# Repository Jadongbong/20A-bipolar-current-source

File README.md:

# Schine Group Bias Coils Current Controller
This repo provides information regarding the Bias Coils Current Controller (here on out referred to as “the controller”) used by the Schine Group at the Joint Quantum Institute (JQI) at University of Maryland, College Park. This is an experimental apparatus designed to drive Helmholtz coil pairs to cancel external magnetic fields which would otherwise disturb the experiment. The controller provides an output current proportional to an input voltage and features an ultra-low noise feedback circuit design for precise control of the output current down to the fractional mA level. The controller has three channels to independently control the magnetic fields along the x, y, and z axes.

## 20A-bipolar-current-source
This project is based on the [`20A-bipolar-current-source`](https://github.com/restelli/20A-bipolar-current-source) design of Mingshu Zhao and Alessandro Restelli. Details on the circuit can be found in their [research article in AIP Advances](https://doi.org/10.1063/5.0138145).

## Circuit files
There are several KiCad project folders within the `kicad` directory in this repo.
* `controller_board` contains the circuit board for the main controller board on which the analog PI feedback is located.
* `Controller_supply` contains the controller's on-board power supply circuit board (used for powering the controller boards)
* `H-bridge` is for the development of the MOT coil current controller (empty project as of Jun 06, 2024).
* `rear` contains the original, liquid-cooled cuircuit board design housing the power MOSFETs that control the coil current. (Not used in this controller)
* `SchineLab_CoilFET_Board` contains the modified, air-cooled circuit board design housing the power MOSFETs for coil current control. (Used in this controller)

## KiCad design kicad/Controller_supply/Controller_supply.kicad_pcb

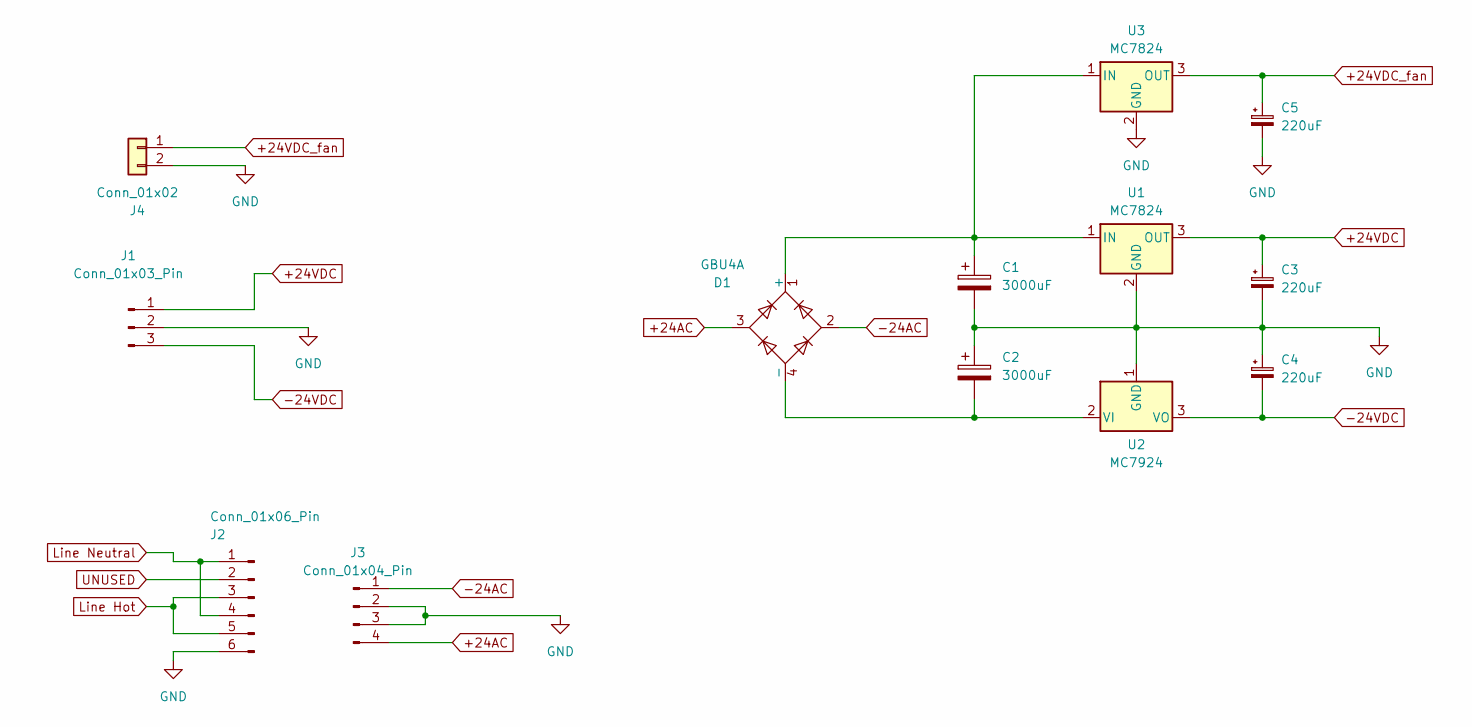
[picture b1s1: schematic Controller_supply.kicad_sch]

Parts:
C1, C2: 3000uF; CP_Elec_18x22; MPN EEE-FK1V302SV; DIGIKEY PARTNO P122523CT-ND
C3, C4, C5: 220uF; CP_Elec_10x10.5; MPN EEE-FK1H221P; DIGIKEY PARTNO PCE3812CT-ND
D1: GBU4A; Diode_Bridge_Vishay_GBU; MPN GBU4A; DIGIKEY PARTNO GBU4A-ND
J1: Conn_01x03_Pin; Generic_10.5x7.5mm-footprt_1x03_P3.50mm_Horizontal
J2: Conn_01x06_Pin
J3: Conn_01x04_Pin; Generic_pin-to-housing_1x04_P5.00mm_Horizontal
J4: Conn_01x02; Generic_7x7.5mm-footprt_1x02_P3.50mm_Horizontal
U1, U3: MC7824; TO-263-2; MPN MC7824CD2TR4G; DIGIKEY PARTNO MC7824CD2TR4GOSCT-ND
U2: MC7924; TO-263-2; MPN MC7924CD2TG; DIGIKEY PARTNO MC7924CD2TG-ND

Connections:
+24AC: D1.3, J3.4
+24VDC: C3.1, J1.1, U1.3 (OUT)
+24VDC_fan: C5.1, J4.1, U3.3 (OUT)
-24AC: D1.2, J3.1
-24VDC: C4.2, J1.3, U2.3 (VO)
GND: C1.2, C2.1, C3.2, C4.1, C5.2, J1.2, J2.6, J3.2, J3.3, J4.2, U1.2 (GND), U2.1 (GND), U3.2 (GND)
unnamed: C1.1, D1.1 (+), U1.1 (IN), U3.1 (IN)
unnamed: J2.1, J2.4
unnamed: J2.3, J2.5
unnamed: C2.2, D1.4 (-), U2.2 (VI)

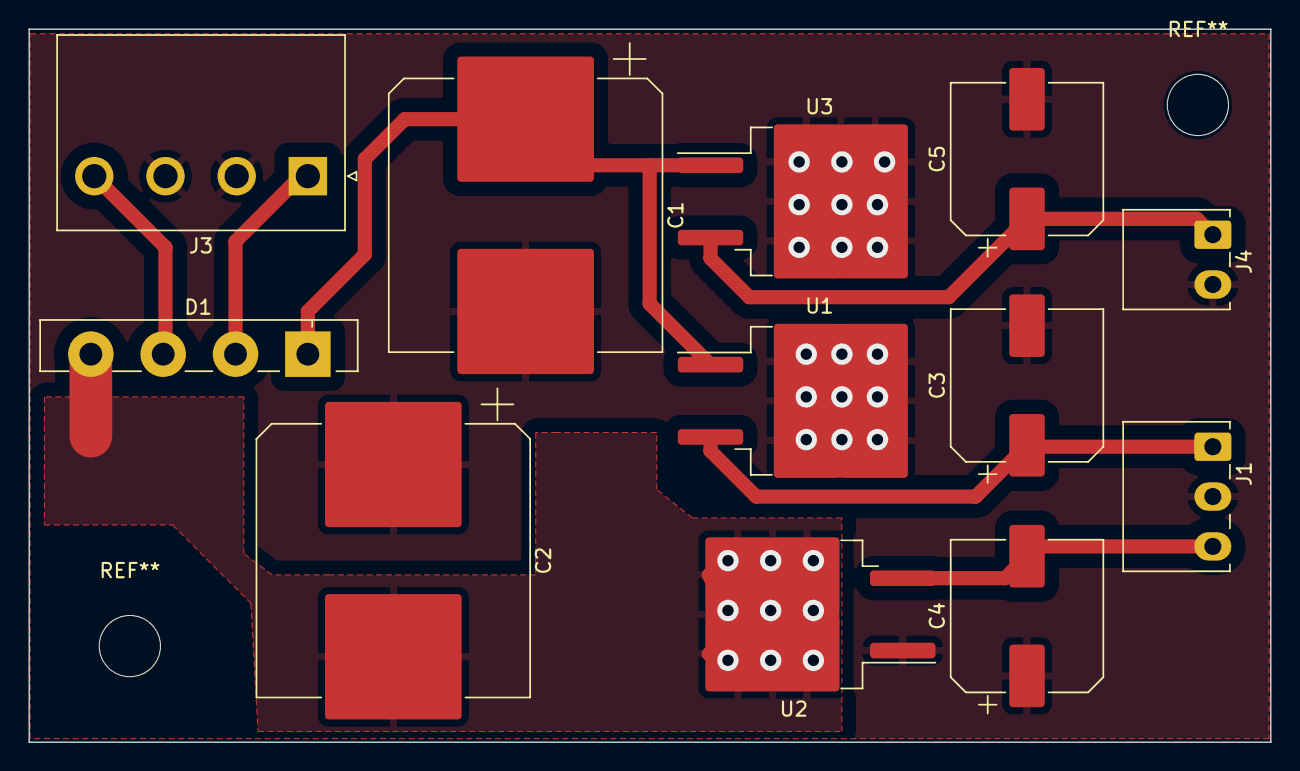
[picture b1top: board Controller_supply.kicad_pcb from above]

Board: 2 copper layers, 87.2 x 50.1 mm, 12 parts (0 on the bottom side), 8 nets.

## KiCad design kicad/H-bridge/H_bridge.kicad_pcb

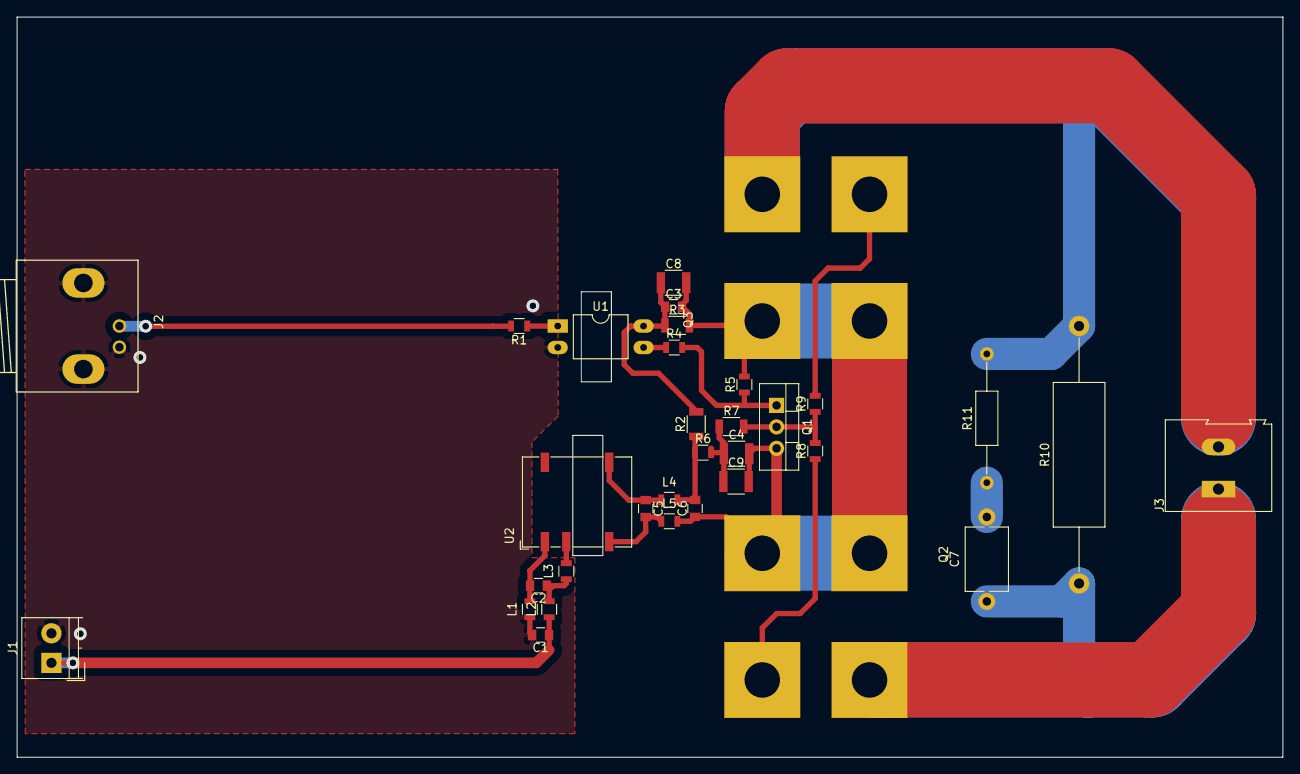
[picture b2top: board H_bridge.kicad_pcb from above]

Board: 2 copper layers, 149.9 x 87.6 mm, 33 parts (0 on the bottom side), 21 nets.

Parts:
C1, C2, C3, C5, C6: C; C_0805
C4, C8, C9: C; C_1210
C7: C; C_Disc_D7.5mm_W5.0mm_P10.00mm
J1: Screw_Terminal_01x02; TerminalBlock_4UCON_19963_02x3.5mm_Straight
J2: Conn_Coaxial; BNC_Socket_TYCO-AMP
J3: Screw_Terminal_01x02; TerminalBlock_Altech_AK300-2_P5.00mm
L1, L2, L3, L4, L5: INDUCTOR; L_0805
Q1: Q_NPN_Darlington_BCE; TO-220-3_Vertical
Q2, Q3: Q_NMOS_GDS; STE250NS10
R1, R4, R5, R6, R8, R9: R_US; R_0805
R2, R3, R7: R_US; R_1206
R10: R_US; R_Axial_DIN0617_L17.0mm_D6.0mm_P30.48mm_Horizontal
R11: R_US; R_Axial_DIN0207_L6.3mm_D2.5mm_P15.24mm_Horizontal
U1: LTV-817; DIP-4_W10.16mm_LongPads
U2: PDS1-S15-S15-M; DCDC-Conv_muRata_NXE2SxxxxMC

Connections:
+15V: C6.2, L4.2, R2.1, R6.1
GND: C1.2, J1.2, J2.2, L1.1, U1.2
GNDD: C3.2, C4.2, C6.1, C8.2, C9.2, L5.2, Q1.3, Q2.3, Q3.3, R3.2, R5.2
unnamed: C1.1, J1.1, L2.1
unnamed: C2.1, L2.2, L3.1
unnamed: C2.2, L1.2, U2.1
unnamed: C3.1, C8.1, R2.2, R3.1, U1.4
unnamed: C4.1, C9.1, R6.2, R7.1
unnamed: C5.1, L4.1, U2.8
unnamed: C5.2, L5.1, U2.7
unnamed: C7.1, J3.1, Q2.2, R10.1
unnamed: C7.2, R11.1
unnamed: J2.1, R1.2
unnamed: J3.2, Q3.2, R10.2, R11.2
unnamed: L3.2, U2.3
unnamed: Q1.1, R4.2, R5.1
unnamed: Q1.2, R7.2, R8.2, R9.1
unnamed: Q2.1, R8.1
unnamed: Q3.1, R9.2
unnamed: R1.1, U1.1
unnamed: R4.1, U1.3

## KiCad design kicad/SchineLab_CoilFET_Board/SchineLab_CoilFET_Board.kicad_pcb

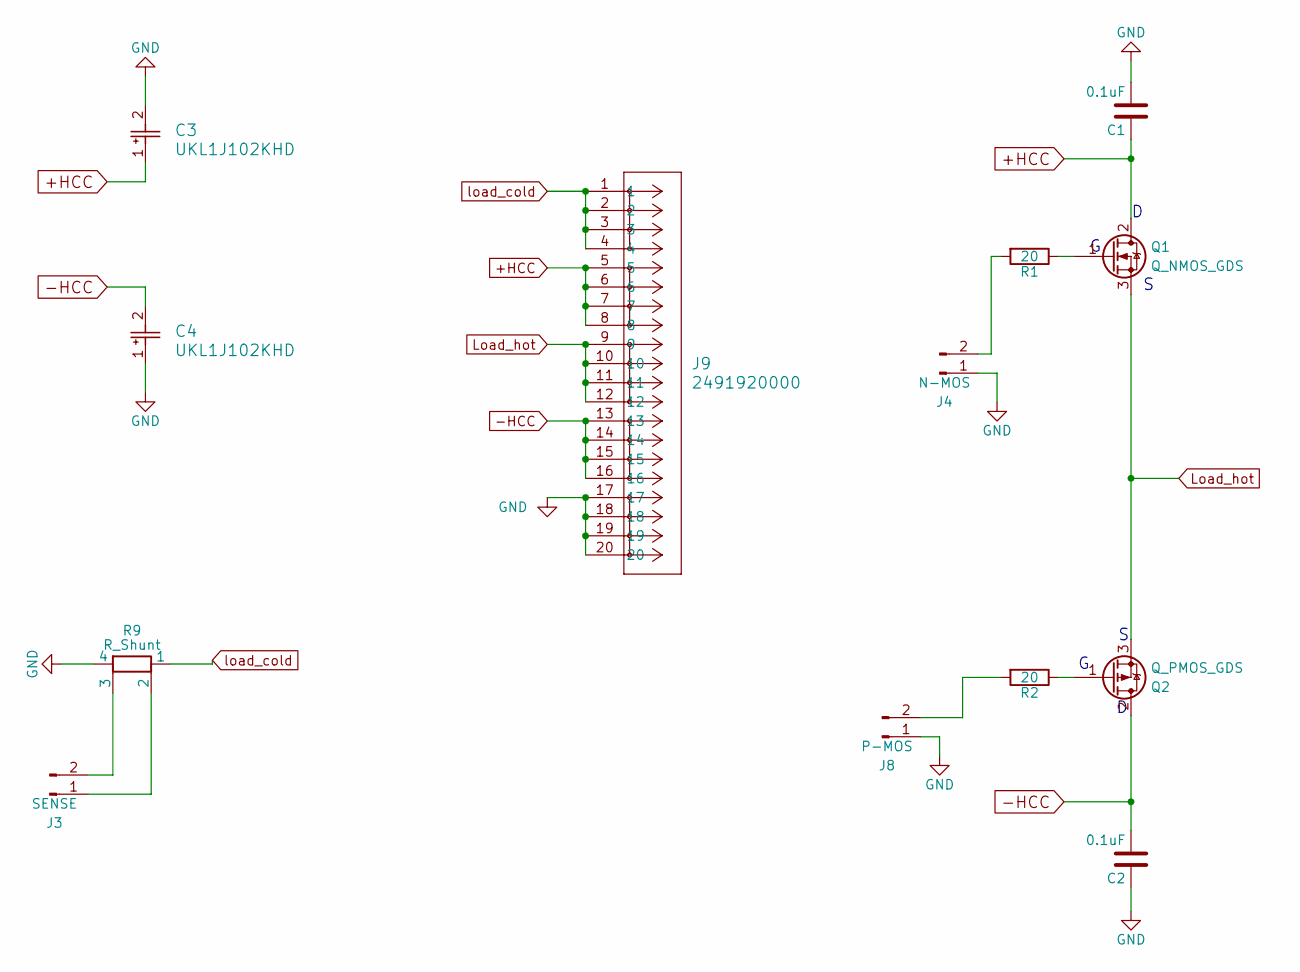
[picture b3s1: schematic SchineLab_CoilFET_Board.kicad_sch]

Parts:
C1, C2: 0.1uF; C_0603_1608Metric; MPN C0603C104J5RACAUTO; DIGIKEY PARTNO 399-6853-1-ND
C3, C4: UKL1J102KHD; CAP_UBY_18X35P5_NCH
J3: SENSE; PinHeader_1x02_P2.54mm_Vertical
J4: N-MOS; PinHeader_1x02_P2.54mm_Vertical
J8: P-MOS; PinHeader_1x02_P2.54mm_Vertical
J9: 2491920000; CONN_249192
Q1: Q_NMOS_GDS; PowerMOS; DIGIKEY PARTNO IXFN520N075T2-ND
Q2: Q_PMOS_GDS; PowerMOS; DIGIKEY PARTNO IXTN170P10P-ND
R1, R2: 20; R_0603_1608Metric_Pad0.98x0.95mm_HandSolder; DIGIKEY PARTNO P20.00BYCT-ND
R9: R_Shunt; SIP-4-ShuntResistor-Riedon

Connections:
+HCC: C1.1, C3.1, J9.5, J9.6, J9.7, J9.8, Q1.2 (D)
-HCC: C2.2, C4.2, J9.13, J9.14, J9.15, J9.16, Q2.2 (D)
GND: C1.2, C2.1, C3.2, C4.1, J4.1, J8.1, J9.17, J9.18, J9.19, J9.20, R9.4
Load_hot: J9.9, J9.10, J9.11, J9.12, Q1.3 (S), Q2.3 (S)
unnamed: J3.1, R9.2
unnamed: J3.2, R9.3
unnamed: J4.2, R1.2
unnamed: J8.2, R2.2
unnamed: Q1.1 (G), R1.1
unnamed: Q2.1 (G), R2.1
load_cold: J9.1, J9.2, J9.3, J9.4, R9.1

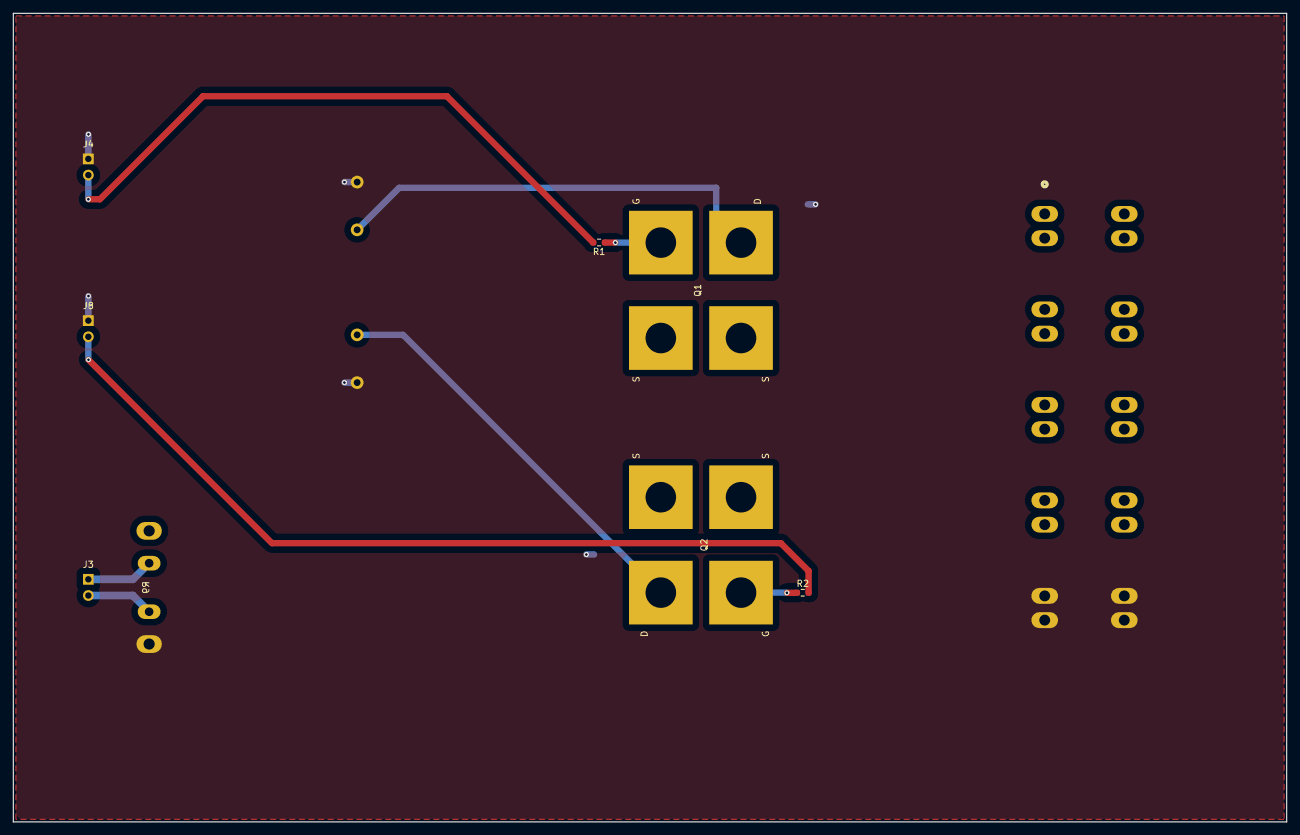
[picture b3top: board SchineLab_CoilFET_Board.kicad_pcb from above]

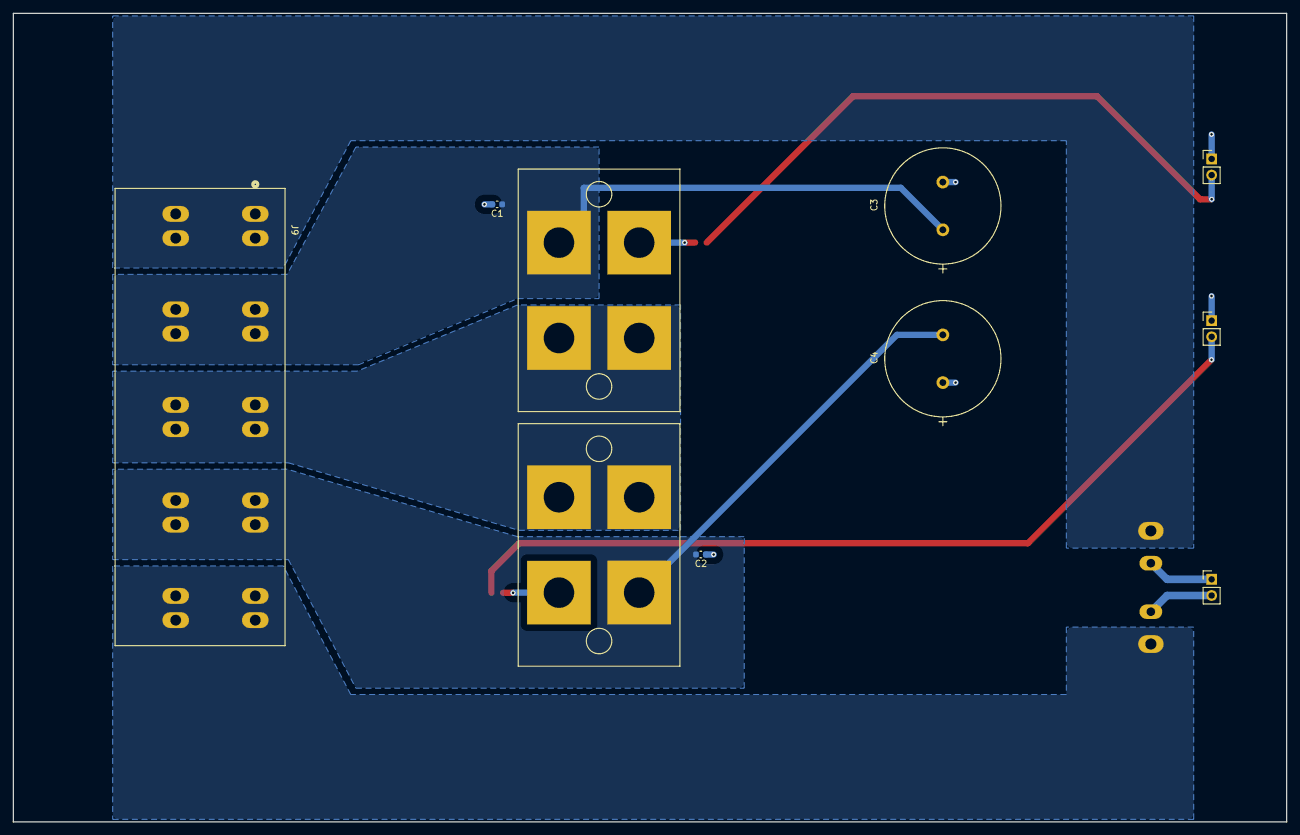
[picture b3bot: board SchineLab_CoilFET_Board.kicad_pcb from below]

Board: 2 copper layers, 200.0 x 127.0 mm, 13 parts (11 on the bottom side), 11 nets.

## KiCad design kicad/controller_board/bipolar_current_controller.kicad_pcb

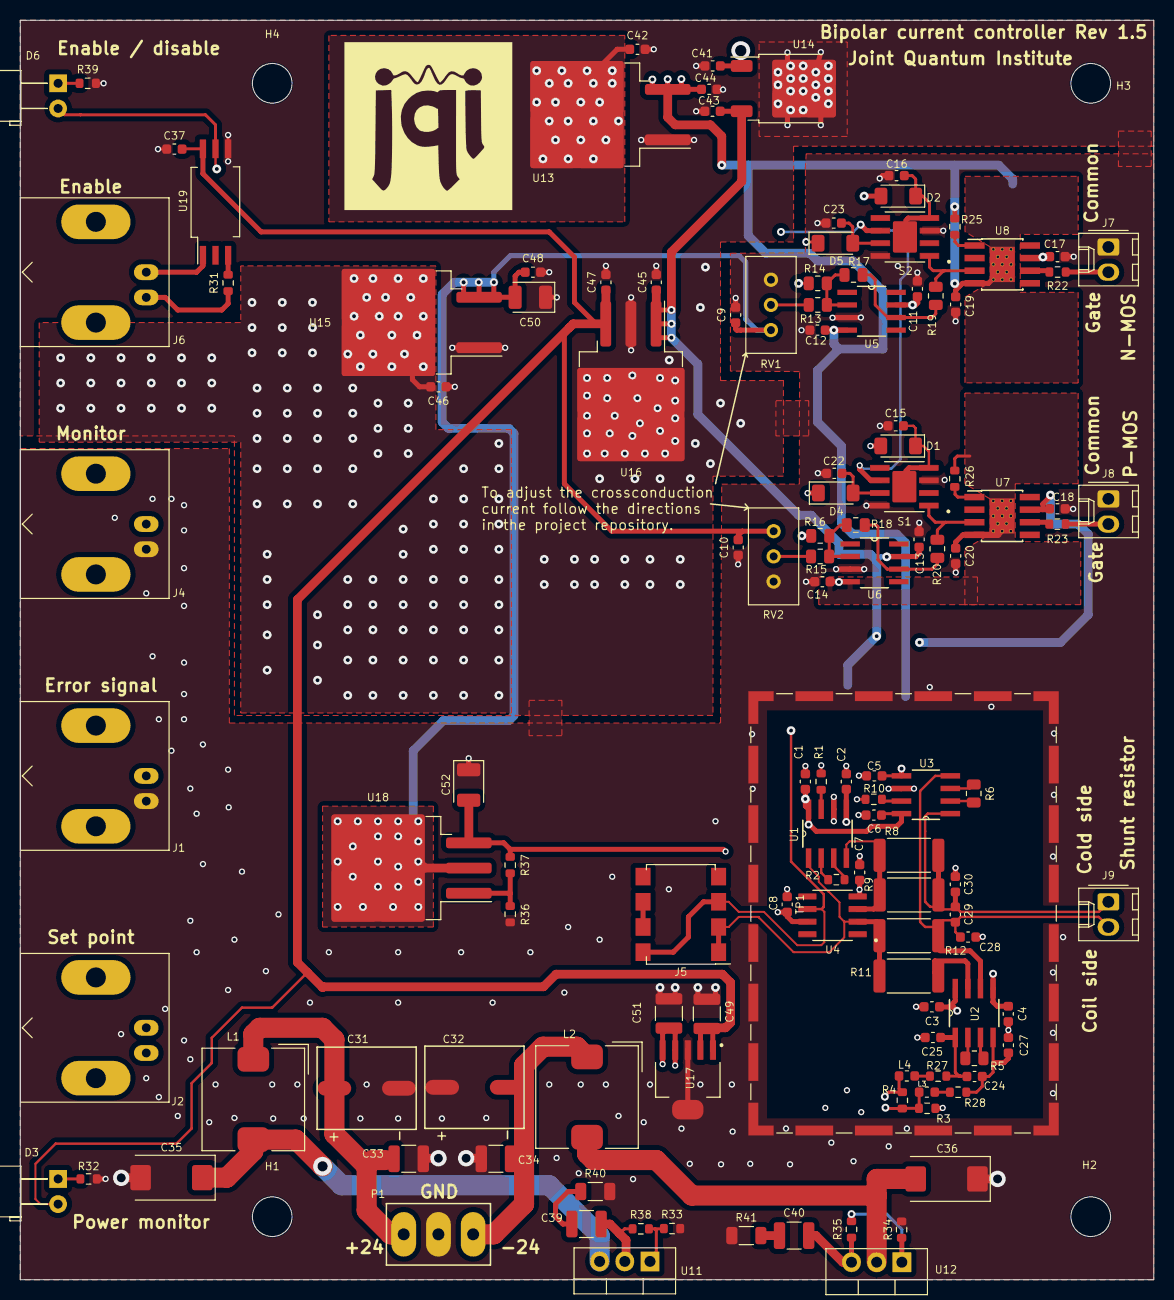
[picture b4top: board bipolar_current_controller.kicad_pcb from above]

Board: 4 copper layers, 114.3 x 127.0 mm, 130 parts (0 on the bottom side), 65 nets.

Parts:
C1, C2, C3, C4, C5, C6, C7, C8, C9, C10, C11, C12, C13, C14, C15, C16, C17, C18, C19, C20, C22, C23, C37, C43, C44, C47, C48: 0.1uF; C_0603_1608Metric
C24, C29: 10n; C_0603_1608Metric
C25, C27, C28, C30: 1n; C_0603_1608Metric
C31, C32: 220uF; CAP_polar_220uF
C33, C34, C39, C40, C49, C51: 10uF; C_1210_3225Metric
C35, C36: 47uF; CP_EIA-7343-43_Kemet-X
C41, C42, C45, C46: 0.33uF; C_0603_1608Metric
C50, C52: 1uF; CP_EIA-3528-21_Kemet-B
D1, D2, D4, D5: D; D_MiniMELF
D3, D6: LED; LED_D5.0mm_Horizontal_O3.81mm_Z3.0mm
H1, H2, H3, H4: MountingHole; MountingHole_4mm
J1: Error signal; BNC_Amphenol_B6252HB-NPP3G-50_Horizontal_mount_float
J2: Set point; BNC_Amphenol_B6252HB-NPP3G-50_Horizontal_mount_float
J4: Monitor; BNC_Amphenol_B6252HB-NPP3G-50_Horizontal_mount_float
J5: Conn_02x04_Counter_Clockwise; SSO-8_7.62x10.1mm_P2.54mm_Clearance8mm
J6: Enable; BNC_Amphenol_B6252HB-NPP3G-50_Horizontal_mount_float
J7: N-MOS; Molex_KK-254_AE-6410-02A_1x02_P2.54mm_Vertical
J8: P-MOS; Molex_KK-254_AE-6410-02A_1x02_P2.54mm_Vertical
J9: Shunt resistor; Molex_KK-254_AE-6410-02A_1x02_P2.54mm_Vertical
L1, L2: 100uH; L_TDK_SLF10145
L3, L4: 1k; L_0603_1608Metric
P1: CONN_01X03; Conn_01X03-3.5mm
R1, R3, R10: 50; R_0603_1608Metric
R2: 200; R_0603_1608Metric
R4: 1M; R_0603_1608Metric
R5: DNP; R_0805_2012Metric
R6: 1k; R_0805_2012Metric
R8, R11: 25k; R_2512_6332Metric
R9, R12: 500; R_2512_6332Metric
R13, R15, R17, R18: 18.2k; R_0805_2012Metric
R14, R16, R19, R20: 2.2k; R_0805_2012Metric
R22, R23: 1; R_0603_1608Metric
R25, R26: DNP; R_0603_1608Metric
R27, R28: 33; R_0603_1608Metric
R31, R32, R39: 1k; R_0603_1608Metric
R33, R34: 1.8k; R_0603_1608Metric
R35, R36, R37, R38: 120; R_0603_1608Metric
R40, R41: 30m; R_1206_3216Metric
RV1, RV2: 1k; Potentiometer_Bourns_3296W_Vertical
S1, S2: MAX4656; MAX4656ESA+
TP1: TestPoint_Small; Laird_Technologies_BMI-S-210-F_44.00x30.50mm
U1, U2, U3: AD8421; AD8421ARZ-R7
U4: OPA388; OPA388IDR
U5, U6: LT1363; LT1363CS8#TRPBF
U7, U8: BUF634A; TI_SO-PowerPAD-8_ThermalVias
U11: LM338; TO-220-3_Vertical
U12: LM337_TO220; TO-220-3_Vertical
U13: LM7915; TO-263-2
U14: uA7815; TO-252-2
U15: LM7905; TO-263-2
U16: LM7805; TO-263-3_TabPin2
U17: TL1963A; TL1963ADCQR
U18: LM337_TO220; TO-263-3_TabPin2
U19: FOD8482TR2; SSO-6_6.8x4.6mm_P1.27mm_Clearance8mm

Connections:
+2V5: C8.2, C51.1, U4.7 (V+), U17.4 (OUT), U17.5 (ADJ)
+5V: C10.2, C37.1, C47.1, C49.1, D3.2 (A), RV2.3, U16.3 (OUT), U17.1 (~SHDN), U17.2 (IN), U19.6 (VCC)
+15V: C1.1, C3.2, C6.2, C13.2, C18.2, C43.1, C45.1, U1.8 (Vs+), U2.8 (Vs+), U3.8 (Vs+), U6.7 (V+), U7.7 (V+), U14.3 (OUT), U16.1 (IN)
+24V: C31.1, C33.1, L1.1, P1.1
-2V5: C7.1, C52.2, R37.2, U4.4 (V-), U18.3 (VO)
-5V: C9.1, C48.2, C50.2, RV1.3, U15.3 (OUT), U18.2 (VI)
-15V: C2.2, C4.1, C5.2, C12.2, C19.1, C44.2, C46.2, R25.2, U1.5 (Vs-), U2.5 (Vs-), U3.5 (Vs-), U5.4 (V-), U8.4 (V-), U8.9 (EP), U13.3 (OUT), U15.2 (IN)
-24V: C32.2, C34.2, L2.1, P1.3
Digital_control: D6.2 (A), S1.6 (IN), S2.6 (IN), U19.5 (VO)
GND: C1.2, C2.1, C3.1, C4.2, C5.1, C6.1, C7.2, C8.1, C9.2, C10.1, C11.1, C12.1, C13.1, C14.1, C15.2, C16.1, C17.1, C18.1, C19.2, C20.2, C22.2, C23.1, C25.1, C27.2, C28.1, C30.2, C31.2, C32.1, C33.2, C34.1, C35.2, C36.1, C37.2, C41.2, C42.1, C43.2, C44.1, C45.2, C46.1, C47.2, C48.1, C49.2, C50.1, C51.2, C52.1, J1.2 (Ext), J4.2 (Ext), J7.1, J8.1, P1.2, R3.2, R32.2, R33.2, R34.1, R36.1, R39.1, R40.2, R41.1, RV1.1, RV2.1, S1.3 (GND), S1.8 (NO), S2.3 (GND), S2.8 (NO), TP1.1, U1.6 (Ref), U3.6 (Ref), U5.3 (+), U6.3 (+), U13.1 (GND), U14.2 (GND), U15.1 (GND), U16.2 (GND), U17.3 (GND), U17.6 (GND), U19.4 (VEE)
unnamed: C39.2, R40.1
unnamed: C40.1, R41.2
unnamed: C15.1, D1.1 (K), S1.4 (V+)
unnamed: C16.2, D2.1 (K), S2.4 (V+)
unnamed: D3.1 (K), R32.1
unnamed: C22.1, D4.2 (A), S1.7 (V-)
unnamed: C23.2, D5.2 (A), S2.7 (V-)
unnamed: D6.1 (K), R39.2
unnamed: J1.1 (In), R1.1
unnamed: J2.2 (Ext), L3.1, R3.1, R4.1
unnamed: J2.1 (In), L4.1, R4.2
unnamed: J4.1 (In), R10.1
unnamed: J5.3, J5.8, R14.2, R16.2, U4.6
unnamed: J5.6, J5.7
unnamed: J6.2 (Ext), R31.1
unnamed: J6.1 (In), U19.1 (A)
unnamed: J7.2, R22.1
unnamed: J8.2, R23.1
unnamed: L3.2, R28.1
unnamed: L4.2, R27.1
unnamed: R1.2, U1.7
unnamed: R2.1, U1.3 (Rg)
unnamed: R2.2, U1.2 (Rg)
unnamed: R5.1, U2.2 (Rg)
unnamed: R5.2, U2.3 (Rg)
unnamed: R6.1, U3.2 (Rg)
unnamed: R6.2, U3.3 (Rg)
unnamed: R10.2, U3.7
unnamed: R11.2, U2.7
unnamed: R13.2, RV1.2
unnamed: R15.2, RV2.2
unnamed: R17.1, R19.2, U5.6
unnamed: R18.1, R20.2, U6.6
unnamed: R20.1, S1.1 (COM1), U7.3 (IN)
unnamed: R19.1, S2.1 (COM1), U8.3 (IN)
unnamed: C24.2, C27.1, R28.2, U2.4 (+)
unnamed: C24.1, C25.2, R27.2, U2.1 (-)
unnamed: R13.1, R14.1, R17.2, U5.2 (-)
unnamed: R15.1, R16.1, R18.2, U6.2 (-)
unnamed: R26.1, U7.1 (BW)
unnamed: R23.2, U7.6 (OUT)
unnamed: R25.1, U8.1 (BW)
unnamed: R22.2, U8.6 (OUT)
unnamed: R33.1, R38.2, U11.1 (ADJ)
unnamed: C35.1, L1.2, U11.3 (VI)
unnamed: R34.2, R35.1, U12.1 (ADJ)
unnamed: C36.2, L2.2, U12.2 (VI)
unnamed: R36.2, R37.1, U18.1 (ADJ)
unnamed: R31.2, U19.3 (C)
POWER_GND_REF: C29.2, C30.1, J9.1, R8.2, R9.2, U3.1 (-)
U1+: R8.1, R9.1, U1.4 (+), U4.3 (+)
U1-: J5.1, J5.2, R11.1, R12.1, U1.1 (-), U4.2 (-)
U2: C28.2, C29.1, J9.2, R12.2, U2.6 (Ref), U3.4 (+)
V+: C11.2, C17.2, C39.1, C41.1, D1.2 (A), D2.2 (A), R38.1, U5.7 (V+), U8.7 (V+), U11.2 (VO), U14.1 (IN)
V-: C14.2, C20.1, C40.2, C42.2, D4.1 (K), D5.1 (K), R26.2, R35.2, U6.4 (V-), U7.4 (V-), U7.9 (EP), U12.3 (VO), U13.2 (IN)

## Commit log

2023-05-22 Corrections of the design after modification of package
    1) The switches were short circuited, I had to remove offending via connections from under the packages.
    2) F.Fab larer has been cleaned up a bit: this will allow for printing a mounting diagram.
    3) In the schematic the GND label has been substituted with teh GND symbol.
    4) Added comments about J5 connector.
    5) Removed .~lock.BOM.csv# that was committed by mistake
2023-05-22 Swap P-MOS and N-MOS labels
2023-06-06 folder rename
2023-06-15 Fixing wrong labels and adding silkscreen
    While testing the board we discovered a wrong labeling for the
    shunt resistor terminals. The board layout is not affected by
    the wrong labeling but a silkscreen needed to be moved.
    The schematic was also updated showing a clearer (and correct) labeling.
    Additionally I added a legend to the board silkscreen showing the
    pinout of the DIL socket.
2023-10-03 Added an example MOS+sensing_resistor board
2023-10-22 Added folder containing modified version of FET board project for Schine lab
2023-11-17 Updtate rear/FET board and added other files
2024-04-22 H-Bridge Schematic
2024-04-22 A few small adjustments
2024-07-19 Updated internal power supply board and rear board.Please
